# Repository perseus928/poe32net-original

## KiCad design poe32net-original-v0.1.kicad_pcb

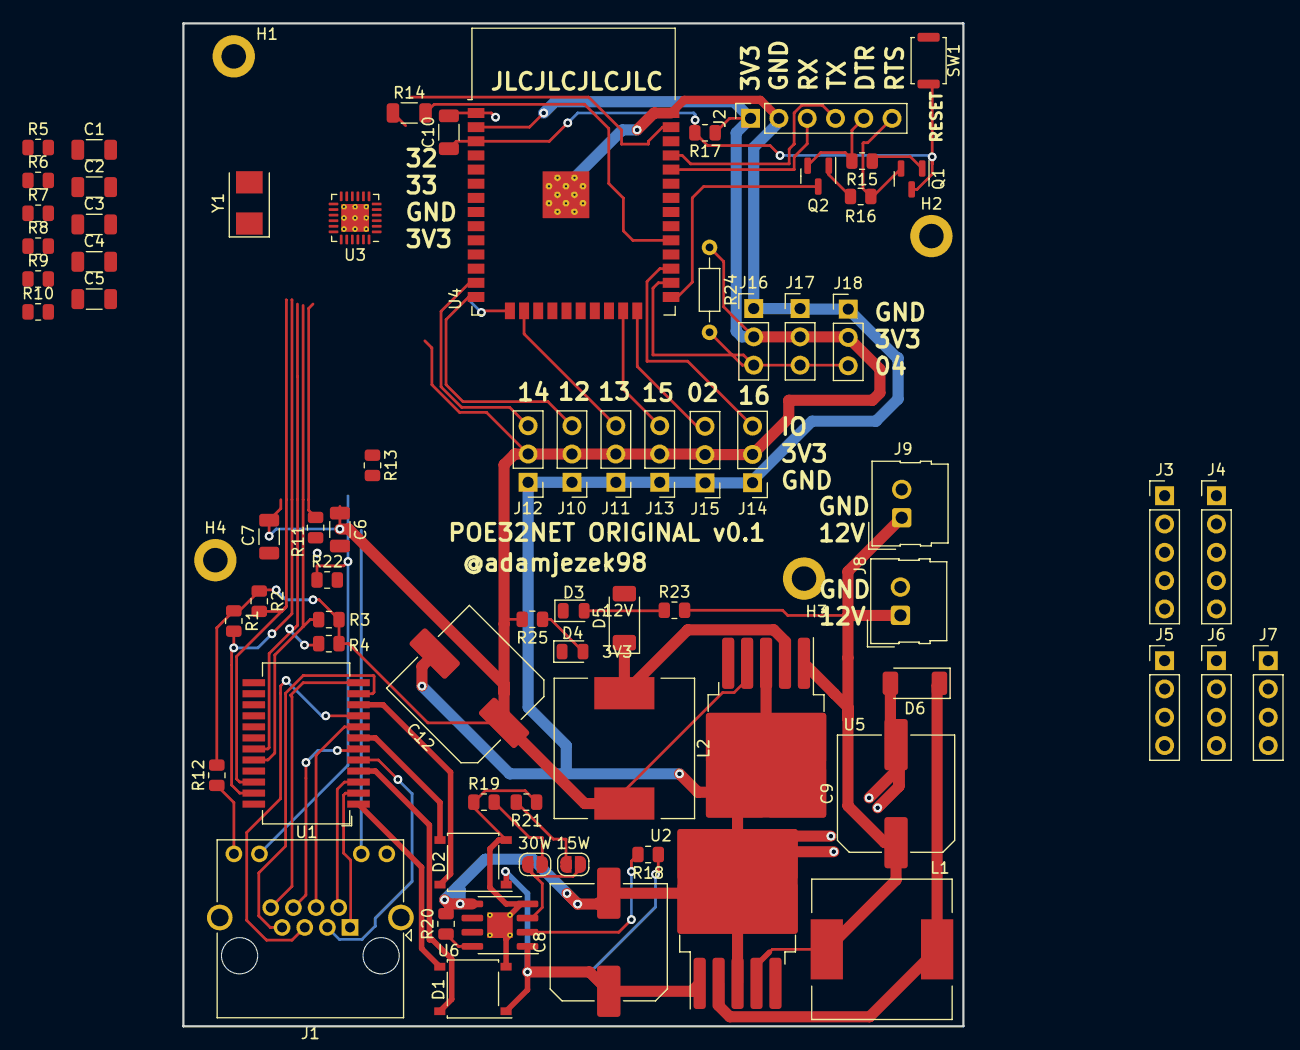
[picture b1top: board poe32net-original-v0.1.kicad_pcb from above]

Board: 2 copper layers, 70.0 x 90.0 mm, 78 parts (0 on the bottom side), 68 nets.

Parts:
C1, C2: 30pF; C_1206_3216Metric
C3, C6, C10: 100nF; C_1206_3216Metric
C4: 10nF; C_1206_3216Metric
C5: 2.2uF; C_1206_3216Metric
C7: 10uF; C_1206_3216Metric
C8: 100uF; C_Elec_10x10.2
C9, C12: 1000uF; C_Elec_10x10.2
D1, D2: D_Bridge_+-AA; Diode_Bridge_Diotec_ABS
D3: LED BLUE; LED_0805_2012Metric
D4: LED GREEN; LED_0805_2012Metric
D5, D6: D_Schottky; D_SOD-128
H1, H2, H3, H4: MountingHole_Pad; MountingHole_2.2mm_M2_DIN965_Pad
J1: RJ45_LED_Shielded; RJ45_Amphenol_RJHSE538X
J2: Conn_01x06_Socket; PinSocket_1x06_P2.54mm_Vertical
J3, J4: Conn_01x05_Pin; PinHeader_1x05_P2.54mm_Vertical
J5, J6, J7: Conn_01x04_Pin; PinHeader_1x04_P2.54mm_Vertical
J8, J9: Conn_01x02; Molex_SL_171971-0002_1x02_P2.54mm_Vertical
J10, J11, J12, J13, J14, J15, J16, J17, J18: 01x03; PinHeader_1x03_P2.54mm_Vertical
JP1: 15W; SolderJumper-2_P1.3mm_Open_RoundedPad1.0x1.5mm
JP2: 30W; SolderJumper-2_P1.3mm_Open_RoundedPad1.0x1.5mm
L1, L2: L; L_12x12mm_H6mm
Q1, Q2: BC817; SOT-23
R1, R2, R3, R4: 49R9; R_0805_2012Metric
R5, R6, R7, R8, R9, R10, R17: 10K; R_0805_2012Metric
R11: 12.1K; R_0805_2012Metric
R12, R13: 68R; R_0805_2012Metric
R14: 0R; R_1206_3216Metric
R15, R16, R20, R22: 10k; R_0805_2012Metric
R18: 25k; R_0805_2012Metric
R19: 63R4; R_0805_2012Metric
R21: 90R9; R_0805_2012Metric
R23: 500R; R_0805_2012Metric
R24: 4K7; R_Axial_DIN0204_L3.6mm_D1.6mm_P7.62mm_Horizontal
R25: 65R; R_0805_2012Metric
SW1: SW_Push; SW_Push_SPST_NO_Alps_SKRK
U1: Transformer_Ethernet_HALO_TG111-MSC13
U2: LM2576HVS-12; TO-263-5_TabPin3
U3: LAN8720A; VQFN-24-1EP_4x4mm_P0.5mm_EP2.5x2.5mm_ThermalVias
U4: ESP32-WROOM-32
U5: LM2576S-3.3; TO-263-5_TabPin3
U6: TPS2378; HSOP-8-1EP_3.9x4.9mm_P1.27mm_EP2.3x2.3mm_ThermalVias
Y1: 25M; Crystal_SMD_5032-2Pin_5.0x3.2mm

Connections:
+3V3: C3.1, C6.1, C7.1, C12.1, J2.1, J3.1, J4.1, J5.1, J6.1, J7.1, J10.2, J11.2, J12.2, J13.2, J14.2, J15.2, J16.2, J17.2, J18.2, L2.2, R1.1, R2.1, R3.1, R4.1, R6.1, R7.1, R8.1, R9.1, R10.1, R12.2, R17.1, R24.1, R25.2, U3.1 (VDD2A), U3.9 (VDDIO), U3.19 (VDD1A), U4.2 (VDD), U5.4 (FB)
+12V: C9.1, J8.1, J9.1, L1.2, R23.2, U2.4 (FB), U5.1 (VIN)
/DTR: J2.5, Q2.2 (E), R15.2
/ESP-EN: C10.1, Q1.3 (C), R17.2, SW1.2, U4.3 (EN)
/ESP-IO0: Q2.3 (C), U4.25 (IO0)
/ESP-RX: J2.3, U4.34 (RXD0/IO3)
/ESP-TX: J2.4, U4.35 (TXD0/IO1)
/ETH-CRS: R8.2, U3.11 (CRS_DV/MODE2), U4.12 (IO27)
/ETH-MDC: U3.13 (MDC), U4.37 (IO23)
/ETH-MDIO: R7.2, U3.12 (MDIO), U4.30 (IO18)
/ETH-RCLK: C1.1, U3.5 (XTAL1/CLKIN), U4.28 (IO17), Y1.2
/ETH-RST: R14.2, U4.29 (IO5)
/ETH-RXD0: R10.2, U3.8 (RXD0/MODE0), U4.10 (IO25)
/ETH-RXD1: R9.2, U3.7 (RXD1/MODE1), U4.11 (IO26)
/ETH-TXD0: U3.17 (TXD0), U4.31 (IO19)
/ETH-TXD1: U3.18 (TXD1), U4.36 (IO22)
/ETH-TXEN: U3.16 (TXEN), U4.33 (IO21)
/GPIO2: J15.3, U4.24 (IO2)
/GPIO4: J16.3, J17.3, J18.3, R24.2, U4.26 (IO4)
/GPIO12: J10.3, U4.14 (IO12)
/GPIO13: J11.3, U4.16 (IO13)
/GPIO14: J12.3, U4.13 (IO14)
/GPIO15: J13.3, U4.23 (IO15)
/GPIO16: J14.3, U4.27 (IO16)
/GPIO32: J3.4, J4.4, J5.4, J6.4, J7.4, U4.8 (IO32)
/GPIO33: J3.3, J4.3, J5.3, J6.3, J7.3, U4.9 (IO33)
/GPIO34: J4.5, U4.6 (IO34)
/GPIO35: J3.5, U4.7 (IO35)
/LED-ETH-1: R13.1, U3.3 (LED1/REGOFF)
/LED-ETH-2: J1.11, R22.1, U3.2 (LED2/~INTSEL)
/RTS: J2.6, Q1.2 (E), R16.2
/RXN: R4.2, U1.19 (MX2-), U3.22 (RXN)
/RXP: R3.2, U1.20 (MX2+), U3.23 (RXP)
/TXN: R2.2, U1.22 (MX1-), U3.20 (TXN)
/TXP: R1.2, U1.23 (MX1+), U3.21 (TXP)
GND: C1.2, C2.2, C3.2, C4.2, C5.1, C6.2, C7.2, C8.2, C9.2, C10.2, C12.2, D3.1 (K), D4.1 (K), D5.2 (A), D6.2 (A), H1.1, H2.1, H3.1, H4.1, J1.9, J1.SH, J2.2, J3.2, J4.2, J5.2, J6.2, J7.2, J8.2, J9.2, J10.1, J11.1, J12.1, J13.1, J14.1, J15.1, J16.1, J17.1, J18.1, R5.2, R11.1, R20.2, R22.2, SW1.1, U2.3 (GND), U2.5 (~ON/OFF), U3.25 (VSS), U4.1 (GND), U4.15 (GND), U4.38 (GND), U4.39 (GND), U5.3 (GND), U5.5 (~ON/OFF), U6.5 (RTN)
unnamed: D3.2 (A), R23.1
unnamed: D4.2 (A), R25.1
unnamed: D5.1 (K), L2.1, U5.2 (OUT)
unnamed: D6.1 (K), L1.1, U2.2 (OUT)
unnamed: J1.10, R13.2
unnamed: J1.12, R12.1
unnamed: JP1.1 (A), R21.2
unnamed: JP1.2 (B), JP2.2 (B), U6.3 (CLS)
unnamed: JP2.1 (A), R19.2
unnamed: Q1.1 (B), R15.1
unnamed: Q2.1 (B), R16.1
unnamed: D1.3, U1.1 (TCT1)
unnamed: D1.4, U1.4 (TCT2)
unnamed: D2.3, U1.7 (TCT3)
unnamed: D2.4, U1.10 (TCT4)
unnamed: J1.1, U1.2 (TD1+)
unnamed: J1.2, U1.3 (TD1-)
unnamed: J1.3, U1.5 (TD2+)
unnamed: J1.6, U1.6 (TD2-)
unnamed: J1.4, U1.8 (TD3+)
unnamed: J1.5, U1.9 (TD3-)
unnamed: J1.7, U1.11 (TD4+)
unnamed: J1.8, U1.12 (TD4-)
unnamed: R11.2, U3.24 (RBIAS)
unnamed: R5.1, U3.10 (RXER/PHYAD0)
unnamed: C4.1, C5.2, U3.6 (VDDCR)
unnamed: C2.1, U3.4 (XTAL2), Y1.1
unnamed: R6.2, R14.1, U3.15 (~RST)
unnamed: R20.1, U6.8 (APD)
unnamed: R18.2, U6.2 (DEN)
POE+: C8.1, D1.1 (+), D2.1 (+), R18.1, U2.1 (VIN), U6.1 (VDD)
POE-: D1.2 (-), D2.2 (-), R19.1, R21.1, U6.4 (VSS), U6.9 (VSS)

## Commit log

2023-04-27 init
2023-08-30 v0.2
